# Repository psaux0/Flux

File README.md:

Flux
====
**Flux** is an open source heating shirt generated at OSL in summer 2014. The basic idea of Flux is to get things like shirt to be online in order to help people with disabilities and their health takers monitor their body temperature change and adjust the heating status responsively. 

###Already Developed

> - Server side Python codes based on Flask and pySerial
> - Microcontroller side codes based on Arduino
> - PCB for wiring

**Flux** comes absolutely with out warranty and it is published under GPL.  
Visit the project page at [Flux](https://psaux0.github.com/Flux)

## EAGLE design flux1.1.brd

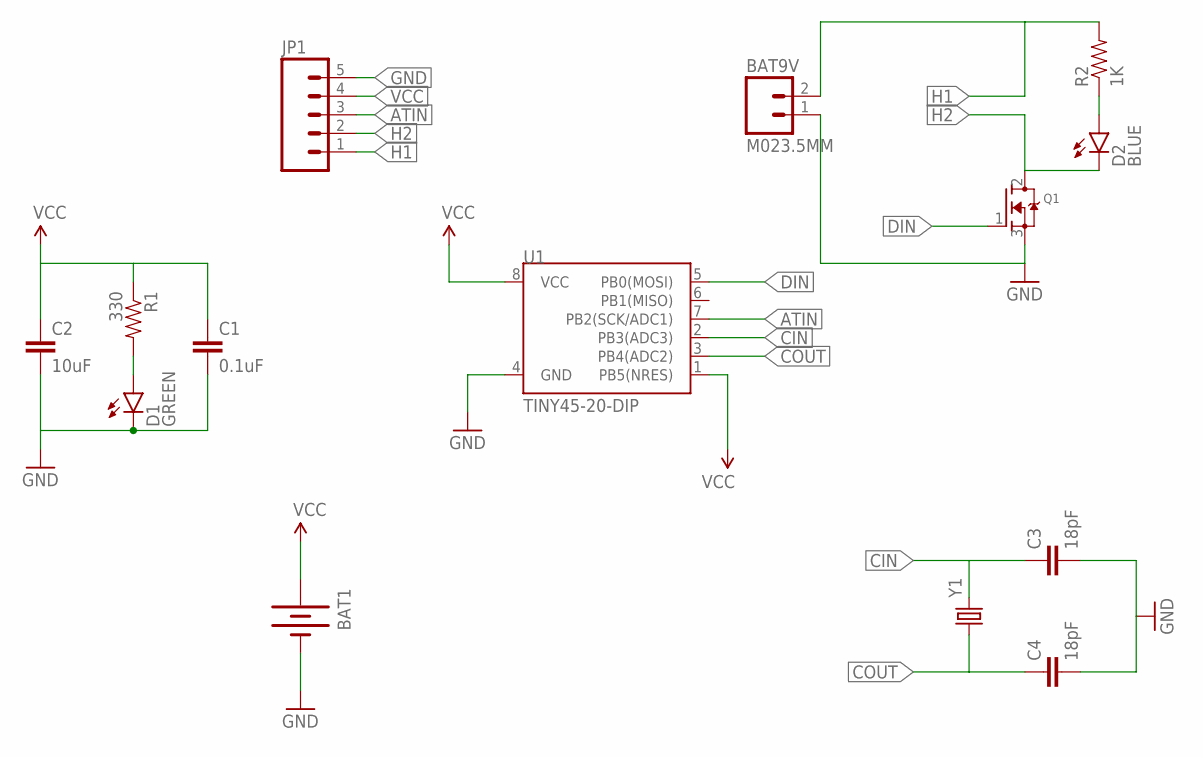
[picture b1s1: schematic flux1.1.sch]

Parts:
BAT1: BATTERY12MM; BATTCON_12MM
BAT9V: M023.5MM; SCREWTERMINAL-3.5MM-2
C1: 0.1uF; 0603-CAP
C2: 10uF; 0603-CAP
C3, C4: 18pF; 0603-CAP
D1: GREEN; LED-0603
D2: BLUE; LED-0603
JP1: M05SMD; 1X05-1MM
Q1: MOSFET-NGDS_TO220V; TO220V
R1: 330; 0603-RES
R2: 1K; 0603-RES
U1: TINY45-20-DIP; DIP08
Y1: CRYSTALHC49US; HC49US

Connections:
ATIN: JP1.3, U1.7 (PB2(SCK/ADC1))
CIN: C3.1, U1.2 (PB3(ADC3)), Y1.2
COUT: C4.1, U1.3 (PB4(ADC2)), Y1.1
DIN: Q1.1 (G), U1.5 (PB0(MOSI))
GND: BAT1.GND (-), BAT9V.1, C1.2, C2.2, C3.2, C4.2, D1.C, JP1.5, Q1.3 (S), U1.4 (GND)
H1: BAT9V.2, JP1.1, R2.2
H2: D2.C, JP1.2, Q1.2 (D)
unnamed: D1.A, R1.2
unnamed: D2.A, R2.1
VCC: BAT1.PWR@1 (+), C1.1, C2.1, JP1.4, R1.1, U1.1 (PB5(NRES)), U1.8 (VCC)

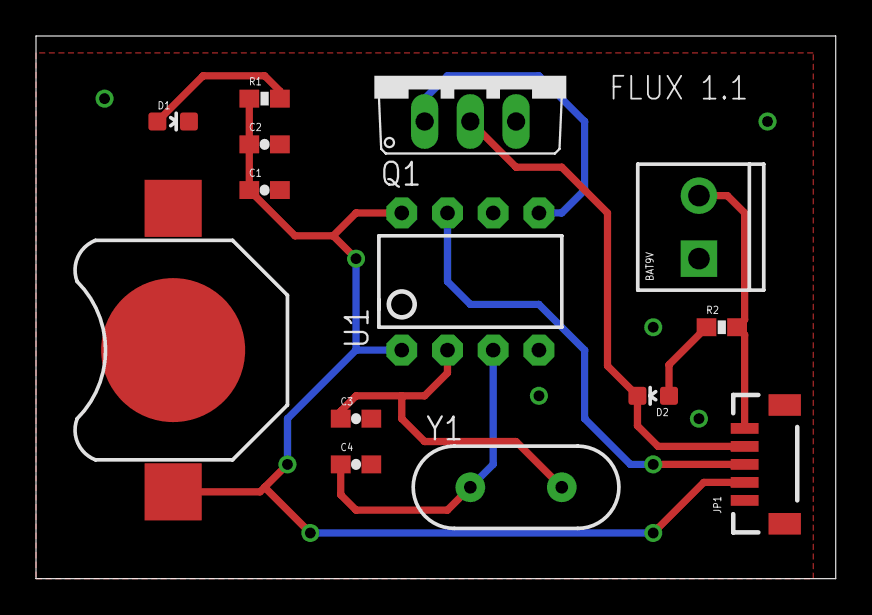
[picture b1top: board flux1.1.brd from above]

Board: 2 copper layers, 44.4 x 30.1 mm, 14 parts (0 on the bottom side), 10 nets.

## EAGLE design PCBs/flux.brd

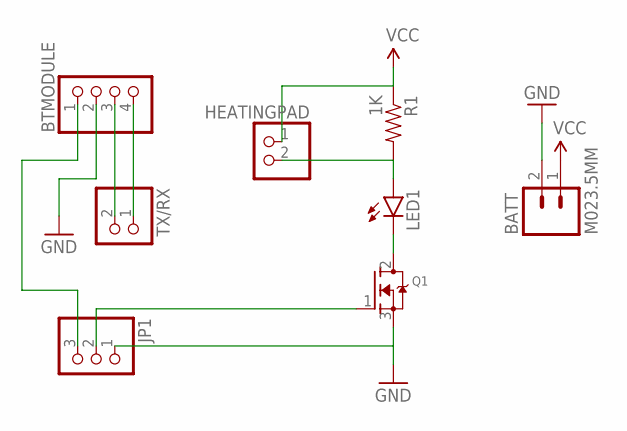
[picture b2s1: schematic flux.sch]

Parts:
BATT: M023.5MM; SCREWTERMINAL-3.5MM-2
BTMODULE: PINHD-1X4; 1X04
HEATINGPAD: PINHD-1X2; 1X02
JP1: PINHD-1X3; 1X03
LED1: LED3MM
Q1: MOSFET-NGDS_TO220V; TO220V
R1: 1K; AXIAL-0.3
TX/RX: PINHD-1X2; 1X02

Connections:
GND: BATT.2, BTMODULE.2, JP1.1, Q1.3 (S)
unnamed: HEATINGPAD.2, LED1.A, R1.P$2 (2)
unnamed: LED1.K (C), Q1.2 (D)
unnamed: BTMODULE.1, JP1.3
unnamed: JP1.2, Q1.1 (G)
unnamed: BTMODULE.3, TX/RX.2
unnamed: BTMODULE.4, TX/RX.1
VCC: BATT.1, HEATINGPAD.1, R1.P$1 (1)

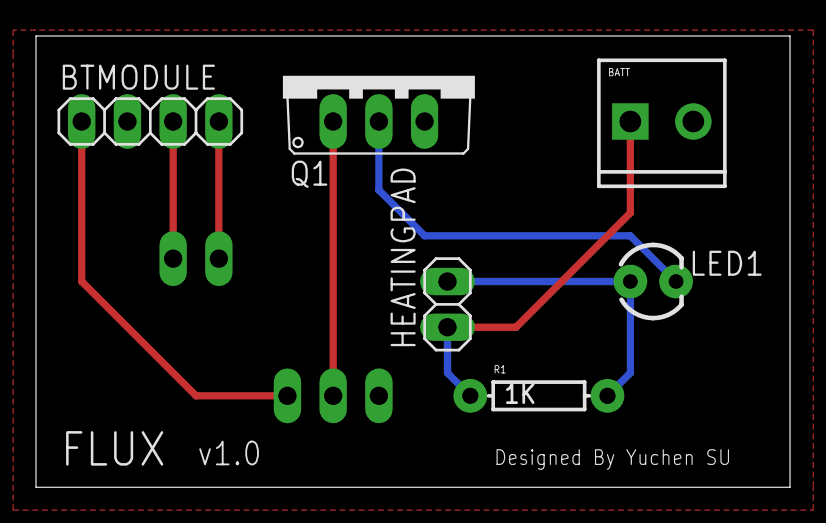
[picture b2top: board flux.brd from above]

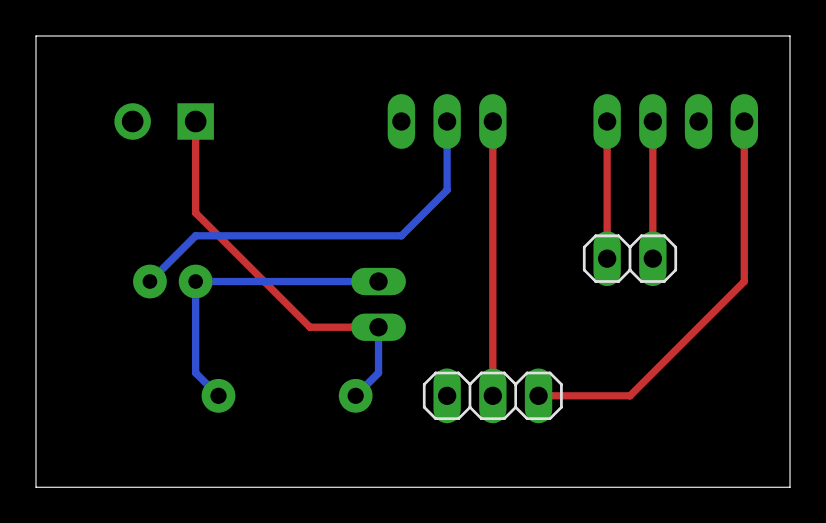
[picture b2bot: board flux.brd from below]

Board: 2 copper layers, 41.9 x 25.1 mm, 8 parts (2 on the bottom side), 8 nets.

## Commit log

2014-10-24 Server side code
2014-10-24 arduino code
2014-10-24 PCB board
2014-11-17 board without arduino
2014-11-17 tiny85 code
2014-11-17 Update: Android App
2014-11-17 update PCB files
2014-11-17 remove
2014-11-17 Images
2014-11-17 project page use
2014-11-17 Create gh-pages branch via GitHub
2014-11-17 Seconde Img
2014-11-18 arduino

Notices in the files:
parts and their libraries:
SparkFun-Connectors: Licensing: Creative Commons ShareAlike 4.0 International - https://creativecommons.org/licenses/by-sa/4.0
